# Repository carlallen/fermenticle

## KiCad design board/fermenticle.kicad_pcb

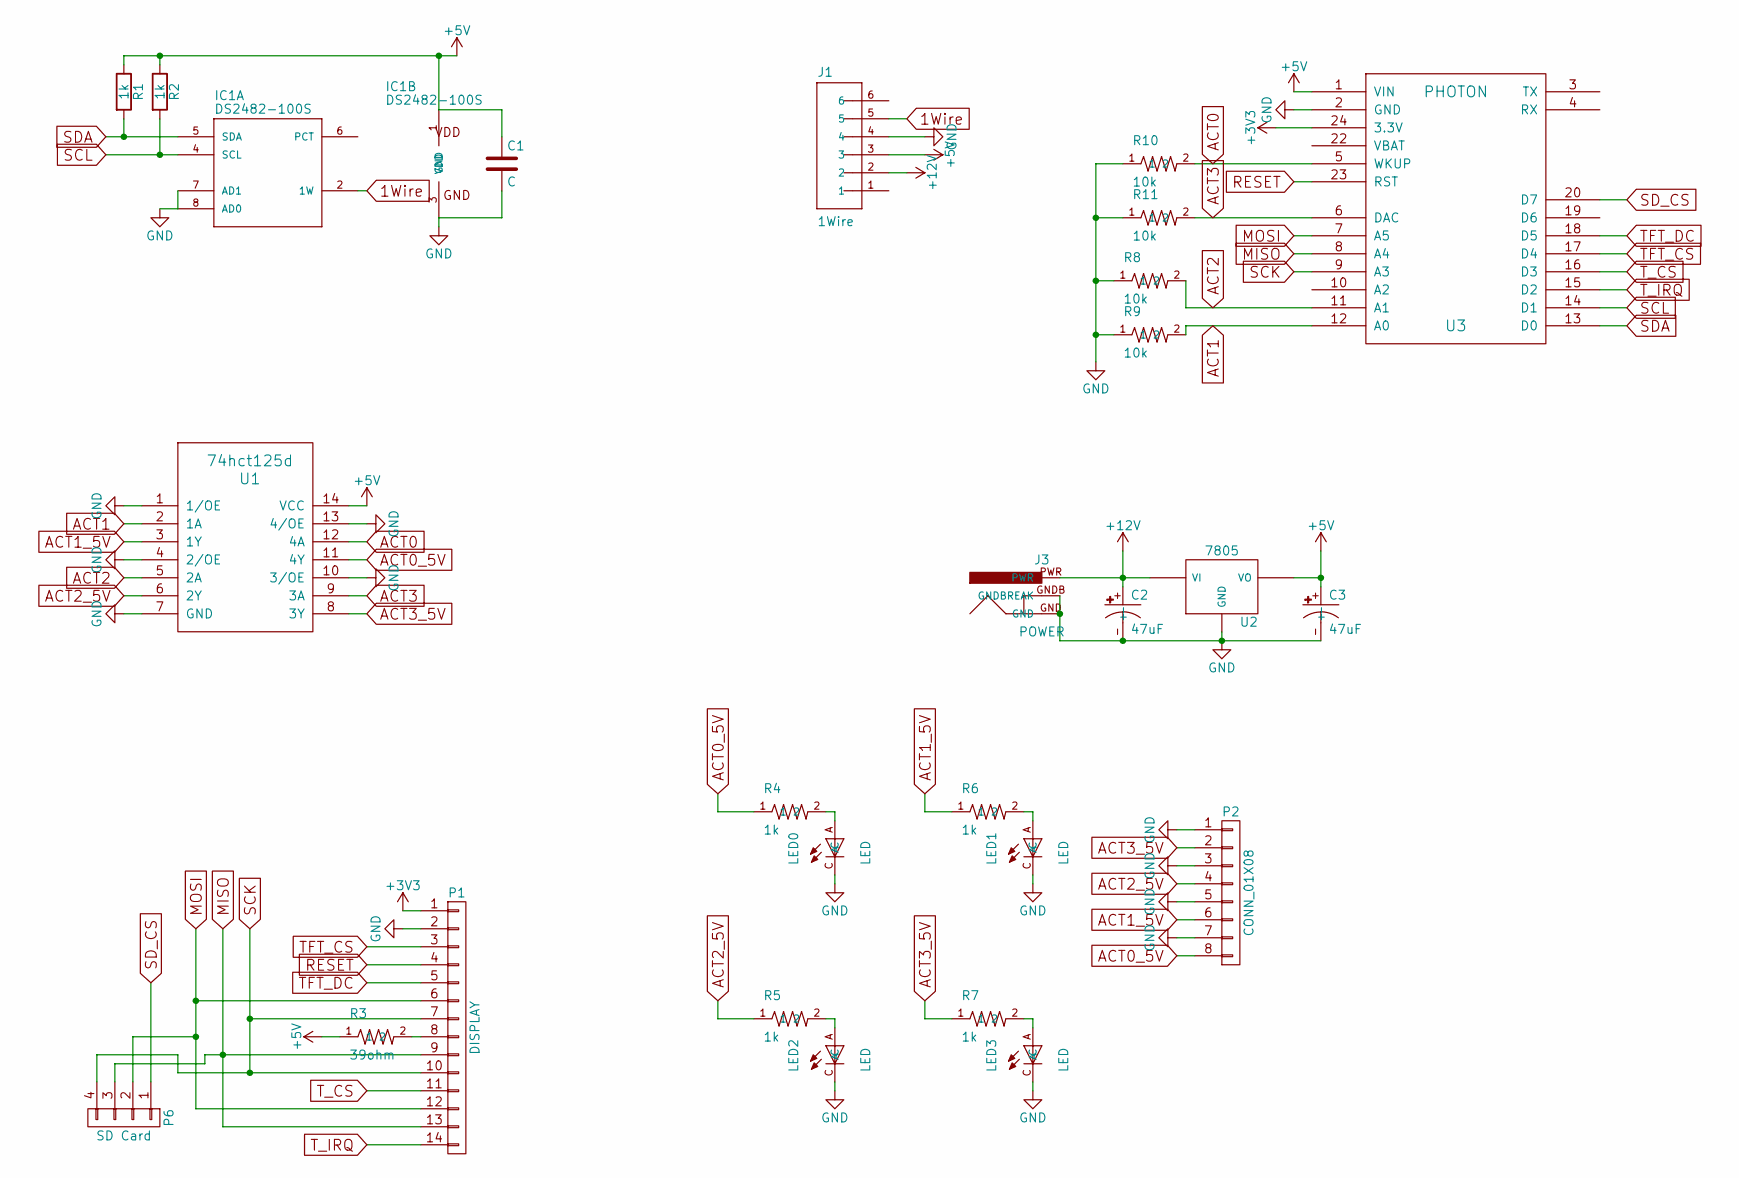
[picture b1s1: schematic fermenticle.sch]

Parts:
C1: C; C_0805_HandSoldering
C2, C3: 47uF; SparkFun-PANASONIC_D
IC1: DS2482-100S; 1wire-SO08
J1: 1Wire; SparkFun-RJ11-6
J3: POWER; SparkFun-POWER_JACK_PTH
LED0, LED1, LED2, LED3: LED; SparkFun-LED-0603
P1: DISPLAY; Socket_Strip_Straight_1x14
P2: CONN_01X08; mstba_2,5%2f8-g-5,08
P6: SD Card; Pin_Header_Angled_1x04
R1, R2, R4, R5, R6, R7: 1k; R_0805_HandSoldering
R3: 39ohm; R_0805_HandSoldering
R8, R9, R10, R11: 10k; R_0805_HandSoldering
U1: 74hct125d; SparkFun-SOIC-14
U2: 7805; SparkFun-V-REG_DPACK
U3: PHOTON

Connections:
1Wire: IC1.2 (1W), J1.5
+3V3: P1.1, U3.24 (3.3V)
+5V: C1.1, C3.+, IC1.1 (VDD), J1.3, R1.1, R2.1, R3.1, U1.14 (VCC), U2.3 (VO), U3.1 (VIN)
+12V: C2.+, J1.2, J3.PWR, U2.1 (VI)
ACT0: R10.2, U1.12 (4A), U3.5 (WKUP)
ACT0_5V: P2.8, R4.1, U1.11 (4Y)
ACT1: R9.2, U1.2 (1A), U3.12 (A0)
ACT1_5V: P2.6, R6.1, U1.3 (1Y)
ACT2: R8.2, U1.5 (2A), U3.11 (A1)
ACT2_5V: P2.4, R5.1, U1.6 (2Y)
ACT3: R11.2, U1.9 (3A), U3.6 (DAC)
ACT3_5V: P2.2, R7.1, U1.8 (3Y)
GND: C1.2, C2.-, C3.-, IC1.3 (GND), IC1.7 (AD1), IC1.8 (AD0), J1.4, J3.GND, J3.GNDB (GNDBREAK), LED0.C, LED1.C, LED2.C, LED3.C, P1.2, P2.1, P2.3, P2.5, P2.7, R8.1, R9.1, R10.1, R11.1, U1.1 (1/OE), U1.4 (2/OE), U1.7 (GND), U1.10 (3/OE), U1.13 (4/OE), U2.4 (GND), U3.2 (GND)
MISO: P1.9, P1.13, P6.3, U3.8 (A4)
MOSI: P1.6, P1.12, P6.2, U3.7 (A5)
unnamed: LED0.A, R4.2
unnamed: LED1.A, R6.2
unnamed: LED2.A, R5.2
unnamed: LED3.A, R7.2
unnamed: P1.8, R3.2
RESET: P1.4, U3.23 (RST)
SCK: P1.7, P1.10, P6.4, U3.9 (A3)
SCL: IC1.4 (SCL), R2.2, U3.14 (D1)
SDA: IC1.5 (SDA), R1.2, U3.13 (D0)
SD_CS: P6.1, U3.20 (D7)
TFT_CS: P1.3, U3.17 (D4)
TFT_DC: P1.5, U3.18 (D5)
T_CS: P1.11, U3.16 (D3)
T_IRQ: P1.14, U3.15 (D2)

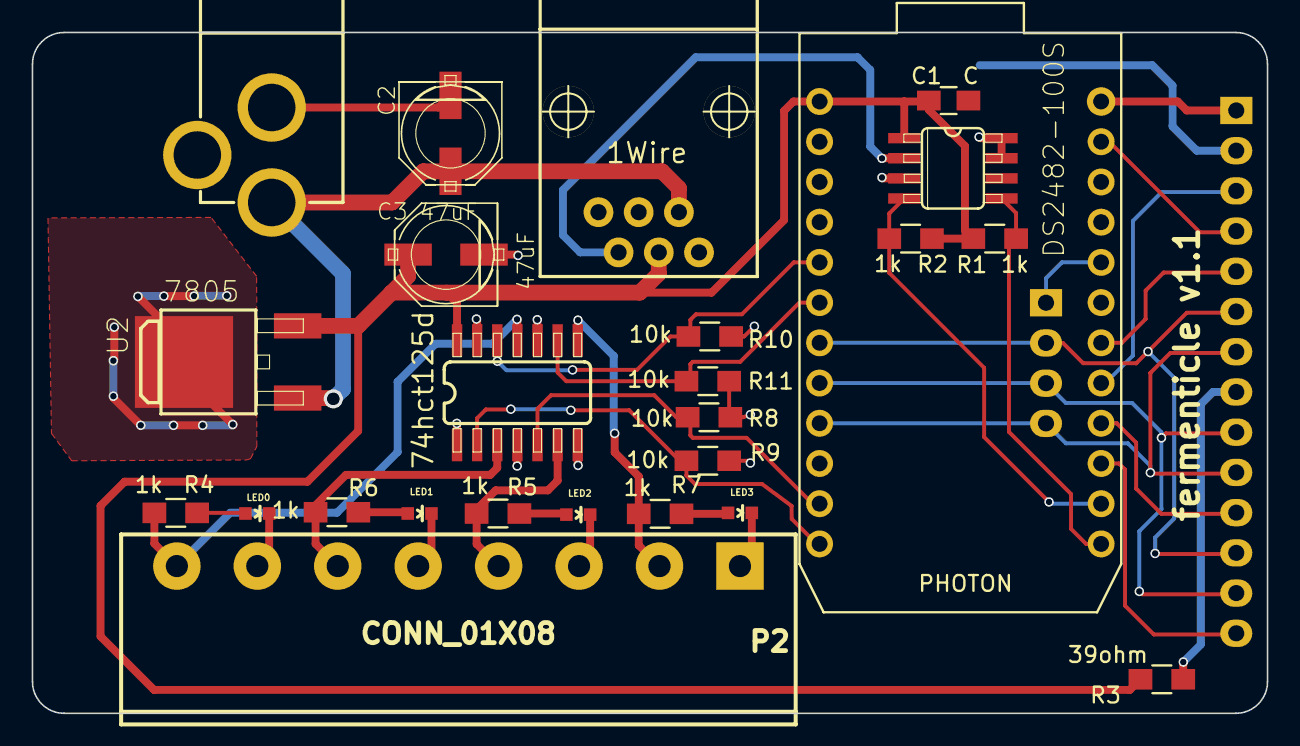
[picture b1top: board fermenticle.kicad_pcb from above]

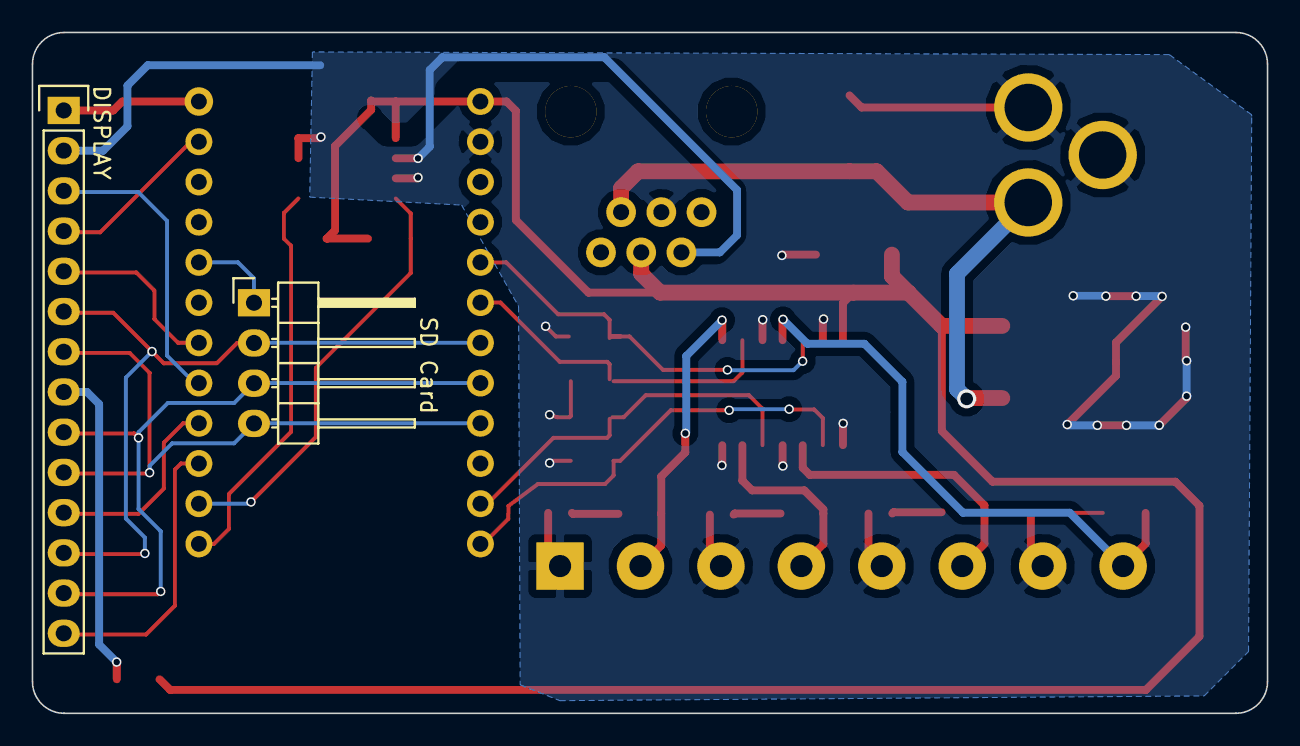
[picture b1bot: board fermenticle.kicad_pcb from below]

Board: 2 copper layers, 78.0 x 43.0 mm, 27 parts (2 on the bottom side), 29 nets.

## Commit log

2016-04-19 Default first sensor for demo development
2016-04-19 Remove readme
2016-04-21 Better 1.1
2016-04-21 Callbacks for home widgets
2016-04-24 Better layout for v1.1
2016-04-24 Ability to set Output devices
2016-04-25 allow setting all base devices
2016-04-25 Store settings in eeprom
2016-05-10 Setpoint adjust buttons
2016-05-10 Make better manager classes
2016-05-12 Temperature Control
